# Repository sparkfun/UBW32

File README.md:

USB 32-Bit Whacker-PIC32MX795 Development Board
================================================

[
*USB 32-Bit Whacker (DEV-09713)*](https://www.sparkfun.com/products/9713)

This breadboard friendly development board enables you to get the PIC32 up and running quickly. 
Power can be provided over USB, there are 3 push buttons (including 2 user-defined buttons),
and 5 indicator LEDs. The board comes pre-loaded with a USB bootloader and special UBW firmware that accepts
simple serial commands to control the various I/O functions. 

Repository Contents
-------------------
* **/Hardware** - All Eagle design files (.brd, .sch, .STL)

License Information
-------------------
Distributed as-is; no warranty is given.

This product is a collaboration with Brian Schmalz.

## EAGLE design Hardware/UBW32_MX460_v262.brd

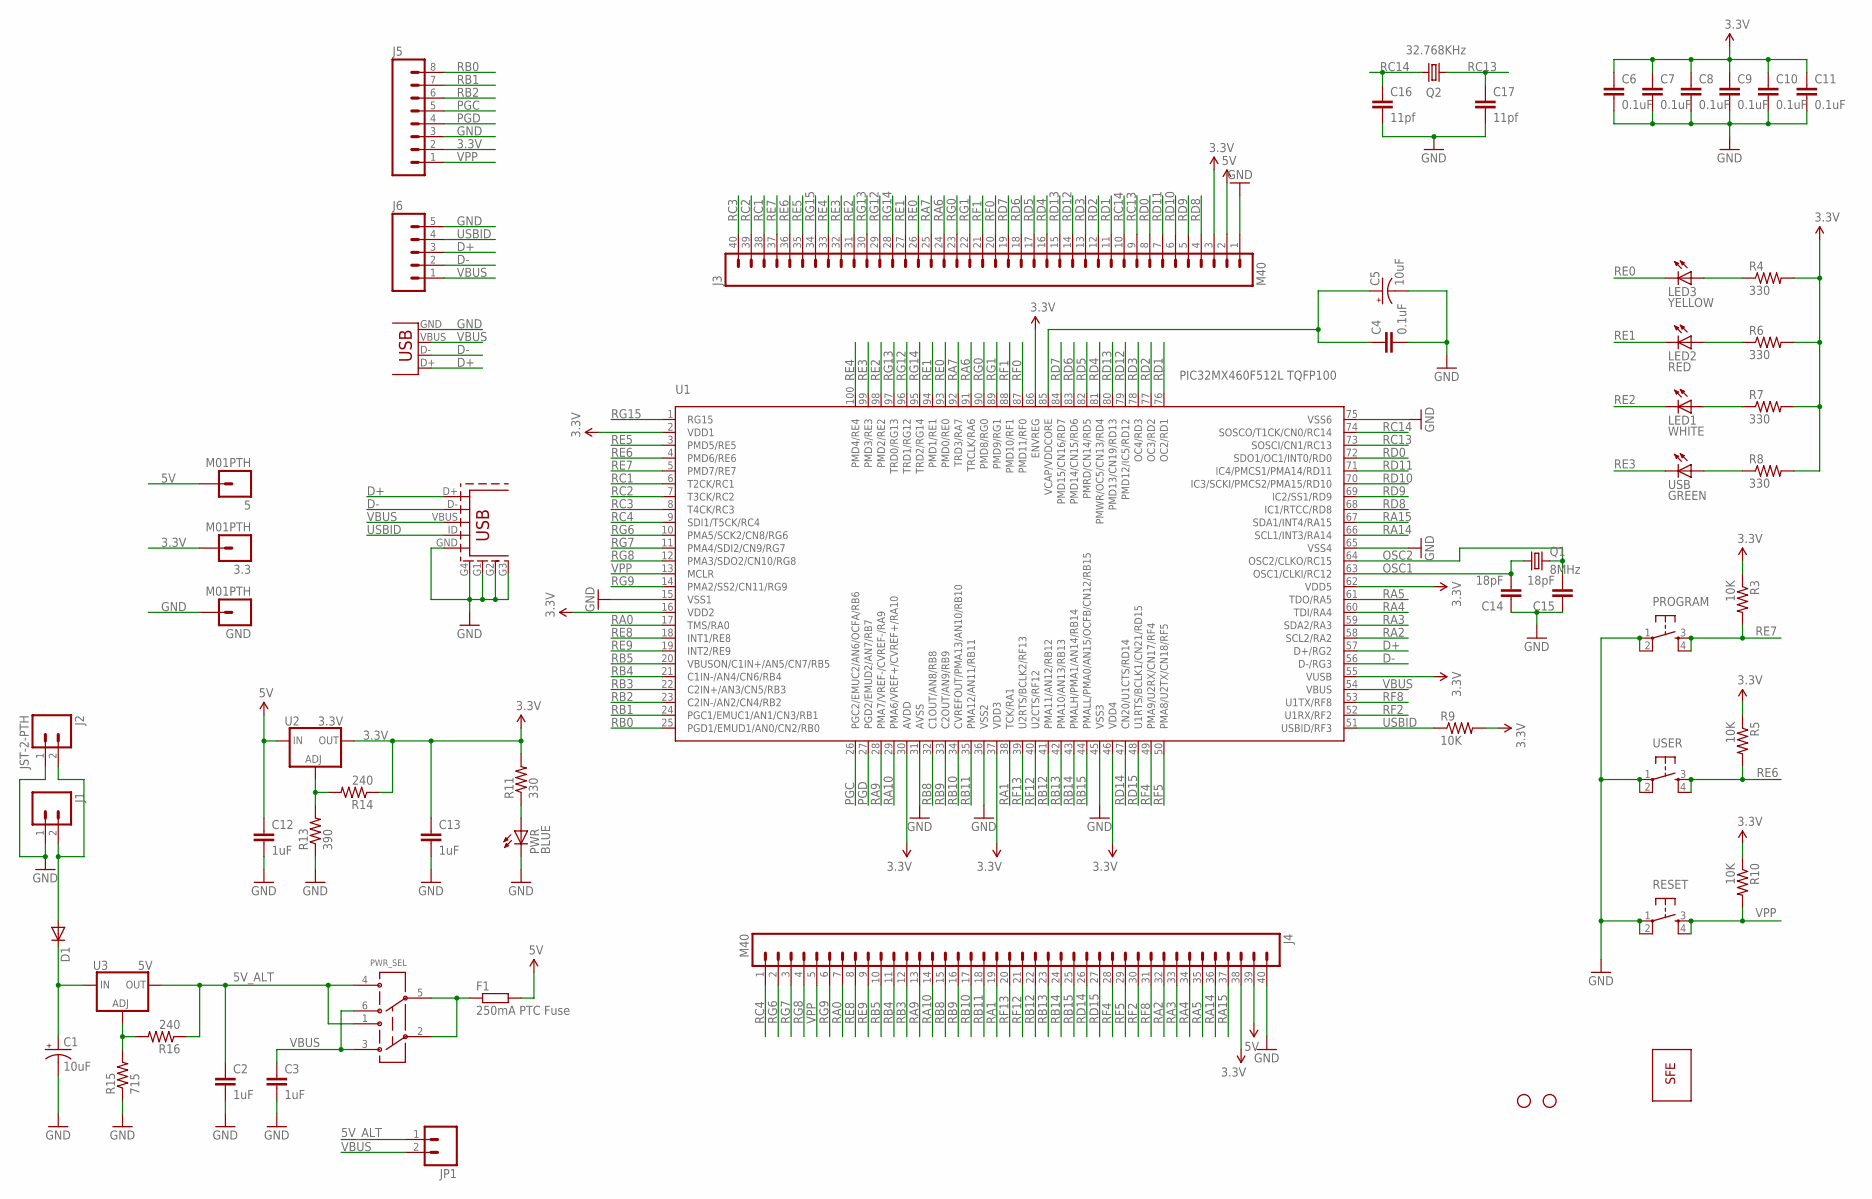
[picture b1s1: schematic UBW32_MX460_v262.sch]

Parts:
3.3, 5: M01PTH; 1X01
C1, C5: 10uF; EIA3528
C2, C3: 1uF; 0402-CAP
C4, C6, C7, C8, C9, C11: 0.1uF; 0402-CAP
C10: 0.1uF; C0402
C12, C13: 1uF; C0402
C14, C15: 18pF; 0402-CAP
C16, C17: 11pf; 0402-CAP
D1: DIODESMA; SMA-DIODE
F1: 250mA PTC Fuse; R1206
GND: M01PTH; 1X01
J1: M02PTH; 1X02
J2: JST-2-PTH; S2B-PH
J3, J4: M40; 1X40
J5: M08; 1X08
J6: M05PTH; 1X05
J7: USB-A-S
J8: USB-MINIB
JP1: M02PTH; 1X02
LED1: WHITE; LED-0603
LED2: RED; LED-0603
LED3: YELLOW; LED-0603
PROGRAM: TAC_SWITCHSND; TACTILE_SWITCH_SMD
PWR: BLUE; LED-0603
PWR_SEL: AYZ0202
Q1: 8MHz; CRYSTAL-SMD-5X3
Q2: 32.768KHz; CRYSTAL-32KHZ-SMD
R3, R5, R9, R10: 10K; 0402-RES
R4, R6, R7, R8, R11: 330; 0402-RES
R13: 390; 0402-RES
R14, R16: 240; 0402-RES
R15: 715; 0402-RES
RESET: TAC_SWITCHSND; TACTILE_SWITCH_SMD
U1: PIC32MX460F512L TQFP100; TQFP100
U2: 3.3V; SOT223
U3: 5V; SOT223
U$4: LOGO-SFENEW; SFE-NEW-WEBLOGO
U$6, U$7: STAND-OFF
USB: GREEN; LED-0603
USER: TAC_SWITCHSND; TACTILE_SWITCH_SMD

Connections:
3.3V: 3.3.1, C6.1, C7.1, C8.1, C9.1, C10.1, C11.1, C13.1, J3.3, J4.38, J5.2, R3.1, R4.2, R5.1, R6.2, R7.2, R8.2, R9.2, R10.1, R11.2, R14.1, U1.2 (VDD1), U1.16 (VDD2), U1.30 (AVDD), U1.37 (VDD3), U1.46 (VDD4), U1.55 (VUSB), U1.62 (VDD5), U1.86 (ENVREG), U2.2 (OUT)
5V: 5.1, C12.1, F1.2, J3.2, J4.39, U2.3 (IN)
5V_ALT: C2.1, JP1.1, PWR_SEL.1 (3), PWR_SEL.4 (6), R16.1, U3.2 (OUT)
D+: J6.3, J7.D+, J8.D+, U1.57 (D+/RG2)
D-: J6.2, J7.D-, J8.D-, U1.56 (D-/RG3)
GND: C1.C (-), C2.2, C3.2, C4.2, C5.C (-), C6.2, C7.2, C8.2, C9.2, C10.2, C11.2, C12.2, C13.2, C14.1, C15.1, C16.2, C17.2, GND.1, J1.1, J2.1, J3.1, J4.40, J5.3, J6.5, J7.GND, J8.G1, J8.G2, J8.G3, J8.G4 (SHIELD), J8.GND, PROGRAM.1, PROGRAM.2, PWR.C, R13.1, R15.1, RESET.1, RESET.2, U1.15 (VSS1), U1.31 (AVSS), U1.36 (VSS2), U1.45 (VSS3), U1.65 (VSS4), U1.75 (VSS6), USER.1, USER.2
unnamed: D1.A, J1.2, J2.2
unnamed: F1.1, PWR_SEL.2, PWR_SEL.5
unnamed: R13.2, R14.2, U2.1 (ADJ)
unnamed: R15.2, R16.2, U3.1 (ADJ)
unnamed: PWR.A, R11.1
unnamed: R8.1, USB.A
unnamed: LED1.A, R7.1
unnamed: LED2.A, R6.1
unnamed: LED3.A, R4.1
unnamed: C4.1, C5.A (+), U1.85 (VCAP/VDDCORE)
OSC1: C14.2, Q1.1, U1.63 (OSC1/CLKI/RC12)
OSC2: C15.2, Q1.3 (2), U1.64 (OSC2/CLKO/RC15)
PGC: J5.5, U1.26 (PGC2/EMUC2/AN6/OCFA/RB6)
PGD: J5.4, U1.27 (PGD2/EMUD2/AN7/RB7)
RA0: J4.7, U1.17 (TMS/RA0)
RA1: J4.19, U1.38 (TCK/RA1)
RA2: J4.32, U1.58 (SCL2/RA2)
RA3: J4.33, U1.59 (SDA2/RA3)
RA4: J4.34, U1.60 (TDI/RA4)
RA5: J4.35, U1.61 (TDO/RA5)
RA6: J3.24, U1.91 (TRCLK/RA6)
RA7: J3.25, U1.92 (TRD3/RA7)
RA9: J4.13, U1.28 (PMA7/VREF-/CVREF-/RA9)
RA10: J4.14, U1.29 (PMA6/VREF+/CVREF+/RA10)
RA14: J4.36, U1.66 (SCL1/INT3/RA14)
RA15: J4.37, U1.67 (SDA1/INT4/RA15)
RB0: J5.8, U1.25 (PGD1/EMUD1/AN0/CN2/RB0)
RB1: J5.7, U1.24 (PGC1/EMUC1/AN1/CN3/RB1)
RB2: J5.6, U1.23 (C2IN-/AN2/CN4/RB2)
RB3: J4.12, U1.22 (C2IN+/AN3/CN5/RB3)
RB4: J4.11, U1.21 (C1IN-/AN4/CN6/RB4)
RB5: J4.10, U1.20 (VBUSON/C1IN+/AN5/CN7/RB5)
RB8: J4.15, U1.32 (C1OUT/AN8/RB8)
RB9: J4.16, U1.33 (C2OUT/AN9/RB9)
RB10: J4.17, U1.34 (CVREFOUT/PMA13/AN10/RB10)
RB11: J4.18, U1.35 (PMA12/AN11/RB11)
RB12: J4.22, U1.41 (PMA11/AN12/RB12)
RB13: J4.23, U1.42 (PMA10/AN13/RB13)
RB14: J4.24, U1.43 (PMALH/PMA1/AN14/RB14)
RB15: J4.25, U1.44 (PMALL/PMA0/AN15/OCFB/CN12/RB15)
RC1: J3.38, U1.6 (T2CK/RC1)
RC2: J3.39, U1.7 (T3CK/RC2)
RC3: J3.40, U1.8 (T4CK/RC3)
RC4: J4.1, U1.9 (SDI1/T5CK/RC4)
RC13: C17.1, J3.9, Q2.X1 (1), U1.73 (SOSCI/CN1/RC13)
RC14: C16.1, J3.10, Q2.X2 (2), U1.74 (SOSCO/T1CK/CN0/RC14)
RD0: J3.8, U1.72 (SDO1/OC1/INT0/RD0)
RD1: J3.11, U1.76 (OC2/RD1)
RD2: J3.12, U1.77 (OC3/RD2)
RD3: J3.13, U1.78 (OC4/RD3)
RD4: J3.16, U1.81 (PMWR/OC5/CN13/RD4)
RD5: J3.17, U1.82 (PMRD/CN14/RD5)
RD6: J3.18, U1.83 (PMD14/CN15/RD6)
RD7: J3.19, U1.84 (PMD15/CN16/RD7)
RD8: J3.4, U1.68 (IC1/RTCC/RD8)
RD9: J3.5, U1.69 (IC2/SS1/RD9)
RD10: J3.6, U1.70 (IC3/SCKI/PMCS2/PMA15/RD10)
RD11: J3.7, U1.71 (IC4/PMCS1/PMA14/RD11)
RD12: J3.14, U1.79 (PMD12/IC5/RD12)
RD13: J3.15, U1.80 (PMD13/CN19/RD13)
RD14: J4.26, U1.47 (CN20/U1CTS/RD14)
RD15: J4.27, U1.48 (U1RTS/BCLK1/CN21/RD15)
RE0: J3.26, LED3.C, U1.93 (PMD0/RE0)
RE1: J3.27, LED2.C, U1.94 (PMD1/RE1)
RE2: J3.31, LED1.C, U1.98 (PMD2/RE2)
RE3: J3.32, U1.99 (PMD3/RE3), USB.C
RE4: J3.33, U1.100 (PMD4/RE4)
RE5: J3.35, U1.3 (PMD5/RE5)
RE6: J3.36, R5.2, U1.4 (PMD6/RE6), USER.3, USER.4
RE7: J3.37, PROGRAM.3, PROGRAM.4, R3.2, U1.5 (PMD7/RE7)
RE8: J4.8, U1.18 (INT1/RE8)
RE9: J4.9, U1.19 (INT2/RE9)
RF0: J3.20, U1.87 (PMD11/RF0)
RF1: J3.21, U1.88 (PMD10/RF1)
RF2: J4.30, U1.52 (U1RX/RF2)
RF4: J4.28, U1.49 (PMA9/U2RX/CN17/RF4)
RF5: J4.29, U1.50 (PMA8/U2TX/CN18/RF5)
RF8: J4.31, U1.53 (U1TX/RF8)
RF12: J4.21, U1.40 (U2CTS/RF12)
RF13: J4.20, U1.39 (U2RTS/BCLK2/RF13)
RG0: J3.23, U1.90 (PMD8/RG0)
RG1: J3.22, U1.89 (PMD9/RG1)
RG6: J4.2, U1.10 (PMA5/SCK2/CN8/RG6)
RG7: J4.3, U1.11 (PMA4/SDI2/CN9/RG7)
RG8: J4.4, U1.12 (PMA3/SDO2/CN10/RG8)
RG9: J4.6, U1.14 (PMA2/SS2/CN11/RG9)
RG12: J3.29, U1.96 (TRD1/RG12)
RG13: J3.30, U1.97 (TRD0/RG13)
RG14: J3.28, U1.95 (TRD2/RG14)
RG15: J3.34, U1.1 (RG15)
USBID: J6.4, J8.ID (USB_ID), R9.1, U1.51 (USBID/RF3)
VBUS: C3.1, J6.1, J7.VBUS, J8.VBUS, JP1.2, PWR_SEL.3 (1), PWR_SEL.6 (4), U1.54 (VBUS)
VIN_RAW: C1.A (+), D1.C, U3.3 (IN)
VPP: J4.5, J5.1, R10.2, RESET.3, RESET.4, U1.13 (MCLR)

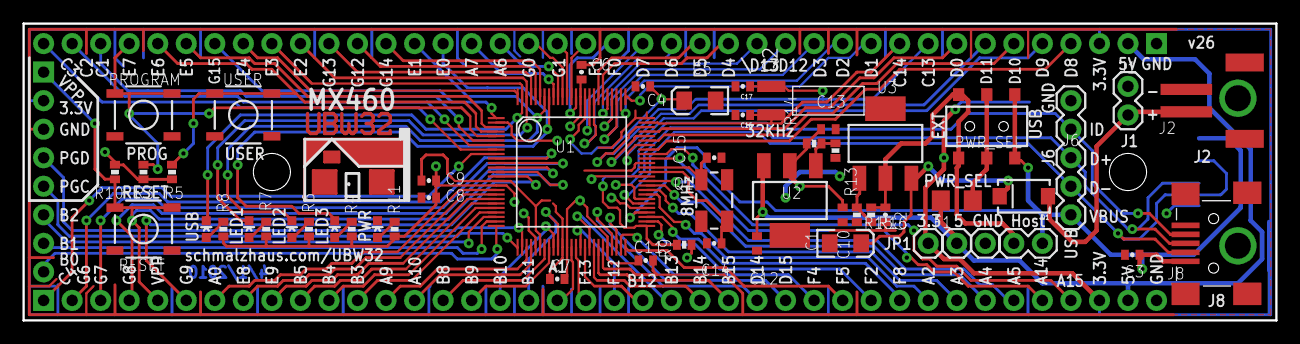
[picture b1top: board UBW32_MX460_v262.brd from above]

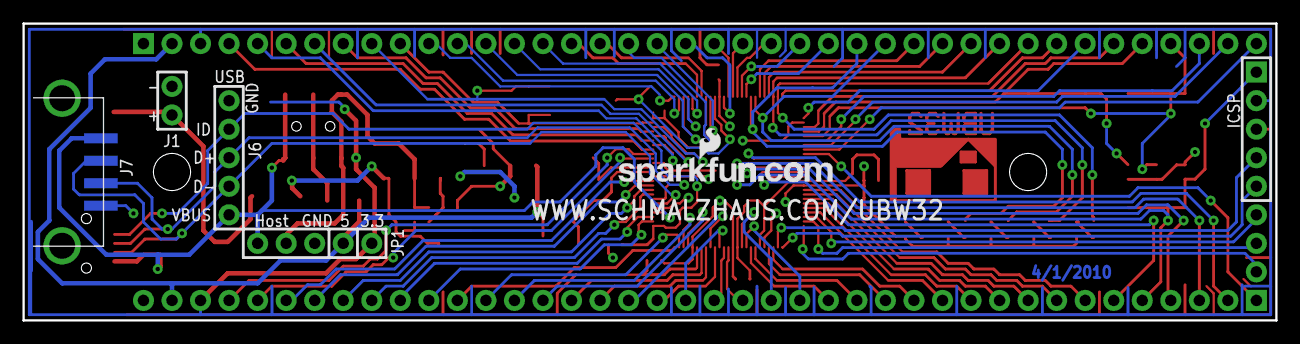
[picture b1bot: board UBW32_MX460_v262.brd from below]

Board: 2 copper layers, 111.5 x 26.4 mm, 63 parts (2 on the bottom side), 100 nets.

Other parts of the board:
U$3: UBW32
U$5: SCHMALZHAUS

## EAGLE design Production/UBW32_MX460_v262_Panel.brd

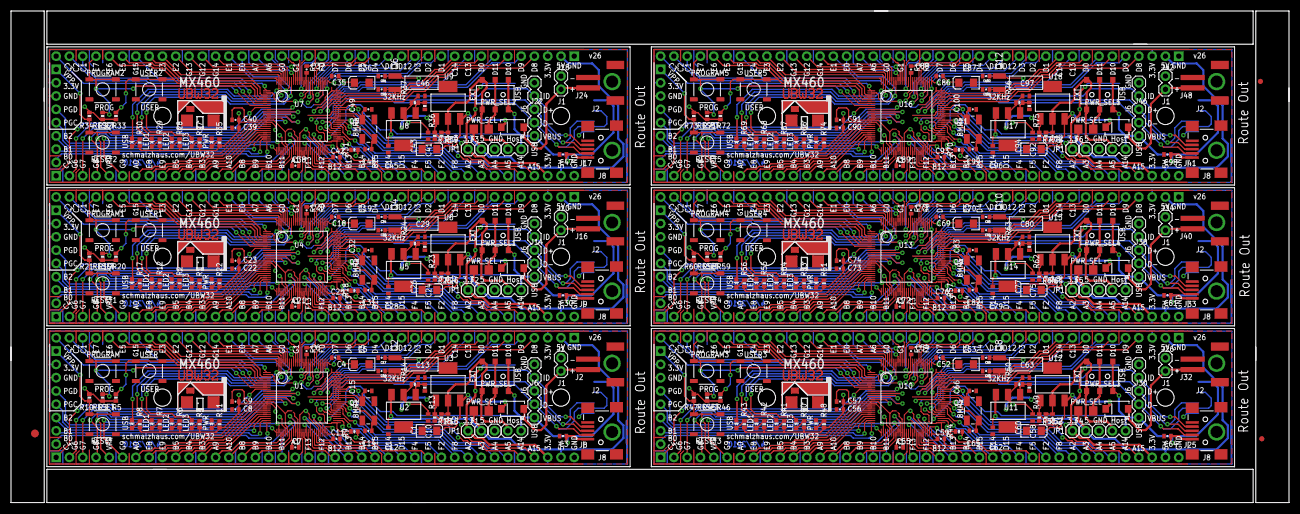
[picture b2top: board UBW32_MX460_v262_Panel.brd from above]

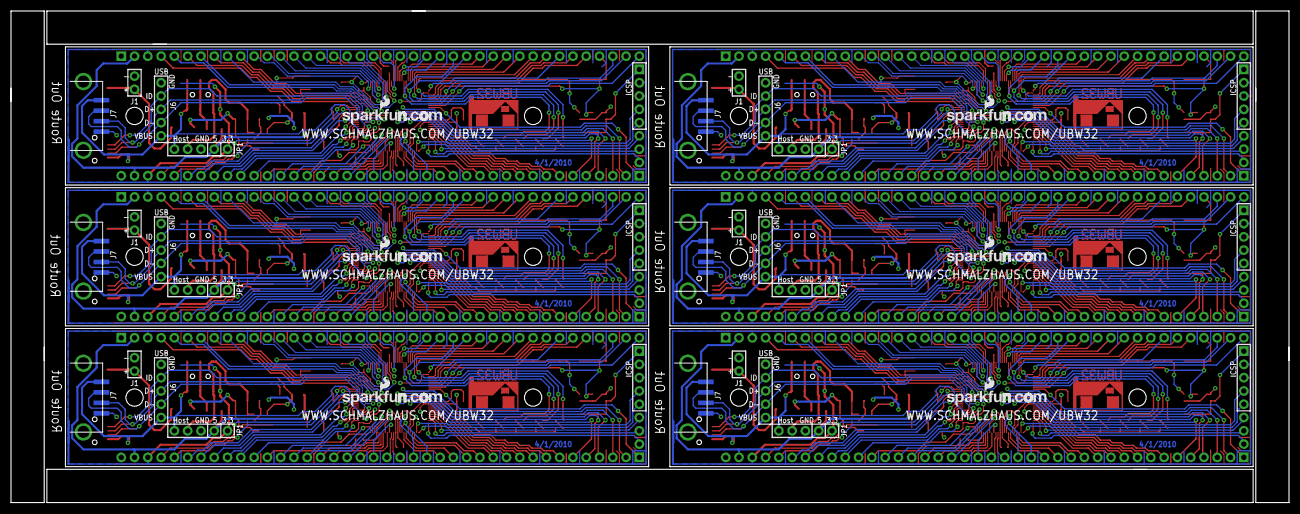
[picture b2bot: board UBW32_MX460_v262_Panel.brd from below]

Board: 2 copper layers, 244.3 x 94.0 mm, 381 parts (12 on the bottom side), 600 nets.

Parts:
1, 2, 3, 3.1, 3.2, 3.3, 3.4, 3.5, 3.6, 4, 5, 6: M01PTH; 1X01
C1, C5, C19, C26, C36, C43, C53, C60, C70, C77, C87, C94: 10uF; EIA3216
C2, C3, C27, C30, C44, C47, C61, C64, C78, C81, C95, C98: 1uF; 0402-CAP
C4, C6, C7, C8, C9, C11, C18, C20, C21, C22, C23, C25, C35, C37, C38, C39, C40, C42, C52, C54, C55, C56, C57, C59, C69, C71, C72, C73, C74, C76, C86, C88, C89, C90, C91, C93: 0.1uF; 0402-CAP
C10, C24, C41, C58, C75, C92: 0.1uF; C0402
C12, C13, C28, C29, C45, C46, C62, C63, C79, C80, C96, C97: 1uF; C0402
C14, C15, C31, C32, C48, C49, C65, C66, C82, C83, C99, C100: 18pF; 0402-CAP
C16, C17, C33, C34, C50, C51, C67, C68, C84, C85, C101, C102: 11pf; 0402-CAP
D1, D2, D3, D4, D5, D6: SMA-DIODE
E$1: FIDUCIAL-1.5X3
E$5, E$6: FIDUCIAL-1X2
F1, F2, F3, F4, F5, F6: 250mA PTC Fuse; R1206
GND, GND1, GND2, GND3, GND4, GND5: M01PTH; 1X01
J1, J10, J18, J26, J34, J42: 1X02
J2, J16, J24, J32, J40, J48: S2B-PH
J3, J4, J11, J12, J19, J20, J27, J28, J35, J36, J43, J44: M40; 1X40
J5, J13, J21, J29, J37, J45: 1X08
J6, J14, J22, J30, J38, J46: 1X05
J7, J15, J23, J31, J39, J47: USB-A-S
J8, J9, J17, J25, J33, J41: USB-MINIB
JP1, JP2, JP3, JP4, JP5, JP6: 1X02
LED1, LED6, LED9, LED12, LED15, LED18: WHITE; LED-0603
LED2, LED5, LED8, LED11, LED14, LED17: RED; LED-0603
LED3, LED4, LED7, LED10, LED13, LED16: YELLOW; LED-0603
PROGRAM, PROGRAM1, PROGRAM2, PROGRAM3, PROGRAM4, PROGRAM5: TACTILE_SWITCH_SMD
PWR, PWR1, PWR2, PWR3, PWR4, PWR5: BLUE; LED-0603
PWR_SEL, PWR_SEL1, PWR_SEL2, PWR_SEL3, PWR_SEL4, PWR_SEL5: AYZ0202
Q1, Q3, Q5, Q7, Q9, Q11: 8MHz; CRYSTAL-SMD-5X3
Q2, Q4, Q6, Q8, Q10, Q12: 32.768KHz; CRYSTAL-32KHZ-SMD
R1, R2, R4, R6, R7, R8, R11, R12, R17, R22, R27, R28, R29, R30, R35, R40, R41, R42, R43, R48, R53, R54, R55, R56, R61, R66, R67, R68, R69, R74: 330; 0402-RES
R3, R5, R9, R10, R18, R19, R20, R21, R31, R32, R33, R34, R44, R45, R46, R47, R57, R58, R59, R60, R70, R71, R72, R73: 10K; 0402-RES
R13, R23, R36, R49, R62, R75: 390; 0402-RES
R14, R16, R24, R26, R37, R39, R50, R52, R63, R65, R76, R78: 240; 0402-RES
R15, R25, R38, R51, R64, R77: 715; 0402-RES
RESET, RESET1, RESET2, RESET3, RESET4, RESET5: TACTILE_SWITCH_SMD
U1, U4, U7, U10, U13, U16: PIC32MX460F512L TQFP100; TQFP100
U2, U5, U8, U11, U14, U17: 3.3V; SOT223
U3, U6, U9, U12, U15, U18: 5V; SOT223
U$1, U$2, U$6, U$7, U$11, U$12, U$16, U$17, U$21, U$22, U$26, U$27: STAND-OFF
U$3, U$9, U$14, U$19, U$24, U$29: UBW32
U$4, U$8, U$13, U$18, U$23, U$28: LOGO-SFENEW; SFE-NEW-WEBLOGO
U$5, U$10, U$15, U$20, U$25, U$30: SCHMALZHAUS
USB, USB1, USB2, USB3, USB4, USB5: GREEN; LED-0603
USER, USER1, USER2, USER3, USER4, USER5: TACTILE_SWITCH_SMD

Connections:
3.3V: 3.3.1, C6.1, C7.1, C8.1, C9.1, C10.1, C11.1, C13.1, J3.3, J4.38, J5.2, R3.1, R4.2, R5.1, R6.2, R7.2, R8.2, R9.2, R10.1, R11.2, R14.1, U1.2, U1.16, U1.30, U1.37, U1.46, U1.55, U1.62, U1.86, U2.2
3.3V1: 3.1.1, C20.1, C21.1, C22.1, C23.1, C24.1, C25.1, C29.1, J11.3, J12.38, J13.2, R1.2, R2.2, R12.2, R17.2, R18.2, R19.1, R20.1, R21.1, R22.2, R24.1, U4.2, U4.16, U4.30, U4.37, U4.46, U4.55, U4.62, U4.86, U5.2
3.3V2: 3.2.1, C37.1, C38.1, C39.1, C40.1, C41.1, C42.1, C46.1, J19.3, J20.38, J21.2, R27.2, R28.2, R29.2, R30.2, R31.2, R32.1, R33.1, R34.1, R35.2, R37.1, U7.2, U7.16, U7.30, U7.37, U7.46, U7.55, U7.62, U7.86, U8.2
3.3V3: 3.4.1, C54.1, C55.1, C56.1, C57.1, C58.1, C59.1, C63.1, J27.3, J28.38, J29.2, R40.2, R41.2, R42.2, R43.2, R44.2, R45.1, R46.1, R47.1, R48.2, R50.1, U10.2, U10.16, U10.30, U10.37, U10.46, U10.55, U10.62, U10.86, U11.2
3.3V4: 3.5.1, C71.1, C72.1, C73.1, C74.1, C75.1, C76.1, C80.1, J35.3, J36.38, J37.2, R53.2, R54.2, R55.2, R56.2, R57.2, R58.1, R59.1, R60.1, R61.2, R63.1, U13.2, U13.16, U13.30, U13.37, U13.46, U13.55, U13.62, U13.86, U14.2
3.3V5: 3.6.1, C88.1, C89.1, C90.1, C91.1, C92.1, C93.1, C97.1, J43.3, J44.38, J45.2, R66.2, R67.2, R68.2, R69.2, R70.2, R71.1, R72.1, R73.1, R74.2, R76.1, U16.2, U16.16, U16.30, U16.37, U16.46, U16.55, U16.62, U16.86, U17.2
5V: 5.1, C12.1, F1.2, J3.2, J4.39, U2.3
5V1: 1.1, C28.1, F2.2, J11.2, J12.39, U5.3
5V2: 2.1, C45.1, F3.2, J19.2, J20.39, U8.3
5V3: 3.1, C62.1, F4.2, J27.2, J28.39, U11.3
5V4: 4.1, C79.1, F5.2, J35.2, J36.39, U14.3
5V5: 6.1, C96.1, F6.2, J43.2, J44.39, U17.3
5V_ALT: C2.1, JP1.1, PWR_SEL.1, PWR_SEL.4, R16.1, U3.2
5V_ALT1: C27.1, JP2.1, PWR_SEL1.1, PWR_SEL1.4, R26.1, U6.2
5V_ALT2: C44.1, JP3.1, PWR_SEL2.1, PWR_SEL2.4, R39.1, U9.2
5V_ALT3: C61.1, JP4.1, PWR_SEL3.1, PWR_SEL3.4, R52.1, U12.2
5V_ALT4: C78.1, JP5.1, PWR_SEL4.1, PWR_SEL4.4, R65.1, U15.2
5V_ALT5: C95.1, JP6.1, PWR_SEL5.1, PWR_SEL5.4, R78.1, U18.2
D+: J6.3, J7.D+, J8.D+, U1.57
D+1: J9.D+, J14.3, J15.D+, U4.57
D+2: J17.D+, J22.3, J23.D+, U7.57
D+3: J25.D+, J30.3, J31.D+, U10.57
D+4: J33.D+, J38.3, J39.D+, U13.57
D+5: J41.D+, J46.3, J47.D+, U16.57
D-: J6.2, J7.D-, J8.D-, U1.56
D-1: J9.D-, J14.2, J15.D-, U4.56
D-2: J17.D-, J22.2, J23.D-, U7.56
D-3: J25.D-, J30.2, J31.D-, U10.56
D-4: J33.D-, J38.2, J39.D-, U13.56
D-5: J41.D-, J46.2, J47.D-, U16.56
GND: C1.C, C2.2, C3.2, C4.2, C5.C, C6.2, C7.2, C8.2, C9.2, C10.2, C11.2, C12.2, C13.2, C14.1, C15.1, C16.2, C17.2, GND.1, J1.1, J2.1, J3.1, J4.40, J5.3, J6.5, J7.GND, J8.G1, J8.G2, J8.G3, J8.G4, J8.GND, PROGRAM.1, PROGRAM.2, PWR.C, R13.1, R15.1, RESET.1, RESET.2, U1.15, U1.31, U1.36, U1.45, U1.65, U1.75, USER.1, USER.2
GND1: C18.2, C19.C, C20.2, C21.2, C22.2, C23.2, C24.2, C25.2, C26.C, C27.2, C28.2, C29.2, C30.2, C31.1, C32.1, C33.2, C34.2, GND1.1, J9.G1, J9.G2, J9.G3, J9.G4, J9.GND, J10.1, J11.1, J12.40, J13.3, J14.5, J15.GND, J16.1, PROGRAM1.1, PROGRAM1.2, PWR1.C, R23.1, R25.1, RESET1.1, RESET1.2, U4.15, U4.31, U4.36, U4.45, U4.65, U4.75, USER1.1, USER1.2
GND2: C35.2, C36.C, C37.2, C38.2, C39.2, C40.2, C41.2, C42.2, C43.C, C44.2, C45.2, C46.2, C47.2, C48.1, C49.1, C50.2, C51.2, GND2.1, J17.G1, J17.G2, J17.G3, J17.G4, J17.GND, J18.1, J19.1, J20.40, J21.3, J22.5, J23.GND, J24.1, PROGRAM2.1, PROGRAM2.2, PWR2.C, R36.1, R38.1, RESET2.1, RESET2.2, U7.15, U7.31, U7.36, U7.45, U7.65, U7.75, USER2.1, USER2.2
GND3: C52.2, C53.C, C54.2, C55.2, C56.2, C57.2, C58.2, C59.2, C60.C, C61.2, C62.2, C63.2, C64.2, C65.1, C66.1, C67.2, C68.2, GND3.1, J25.G1, J25.G2, J25.G3, J25.G4, J25.GND, J26.1, J27.1, J28.40, J29.3, J30.5, J31.GND, J32.1, PROGRAM3.1, PROGRAM3.2, PWR3.C, R49.1, R51.1, RESET3.1, RESET3.2, U10.15, U10.31, U10.36, U10.45, U10.65, U10.75, USER3.1, USER3.2
GND4: C69.2, C70.C, C71.2, C72.2, C73.2, C74.2, C75.2, C76.2, C77.C, C78.2, C79.2, C80.2, C81.2, C82.1, C83.1, C84.2, C85.2, GND4.1, J33.G1, J33.G2, J33.G3, J33.G4, J33.GND, J34.1, J35.1, J36.40, J37.3, J38.5, J39.GND, J40.1, PROGRAM4.1, PROGRAM4.2, PWR4.C, R62.1, R64.1, RESET4.1, RESET4.2, U13.15, U13.31, U13.36, U13.45, U13.65, U13.75, USER4.1, USER4.2
GND5: C86.2, C87.C, C88.2, C89.2, C90.2, C91.2, C92.2, C93.2, C94.C, C95.2, C96.2, C97.2, C98.2, C99.1, C100.1, C101.2, C102.2, GND5.1, J41.G1, J41.G2, J41.G3, J41.G4, J41.GND, J42.1, J43.1, J44.40, J45.3, J46.5, J47.GND, J48.1, PROGRAM5.1, PROGRAM5.2, PWR5.C, R75.1, R77.1, RESET5.1, RESET5.2, U16.15, U16.31, U16.36, U16.45, U16.65, U16.75, USER5.1, USER5.2
unnamed: D1.A, J1.2, J2.2
unnamed: F1.1, PWR_SEL.2, PWR_SEL.5
unnamed: R13.2, R14.2, U2.1
unnamed: R15.2, R16.2, U3.1
unnamed: C18.1, C19.A, U4.85
unnamed: PWR.A, R11.1
unnamed: R17.1, USB1.A
unnamed: LED6.A, R12.1
unnamed: LED5.A, R2.1
unnamed: LED4.A, R1.1
unnamed: PWR1.A, R22.1
unnamed: D2.A, J10.2, J16.2
unnamed: F2.1, PWR_SEL1.2, PWR_SEL1.5
unnamed: R23.2, R24.2, U5.1
unnamed: R25.2, R26.2, U6.1
unnamed: C35.1, C36.A, U7.85
unnamed: R30.1, USB2.A
unnamed: LED9.A, R29.1
unnamed: LED8.A, R28.1
unnamed: R8.1, USB.A
unnamed: LED7.A, R27.1
unnamed: LED1.A, R7.1
unnamed: LED2.A, R6.1
unnamed: PWR2.A, R35.1
unnamed: D3.A, J18.2, J24.2
unnamed: F3.1, PWR_SEL2.2, PWR_SEL2.5
unnamed: R36.2, R37.2, U8.1
unnamed: R38.2, R39.2, U9.1
unnamed: C52.1, C53.A, U10.85
unnamed: R43.1, USB3.A
unnamed: LED12.A, R42.1
unnamed: LED11.A, R41.1
unnamed: LED10.A, R40.1
unnamed: PWR3.A, R48.1
unnamed: LED3.A, R4.1
unnamed: D4.A, J26.2, J32.2
unnamed: F4.1, PWR_SEL3.2, PWR_SEL3.5
unnamed: R49.2, R50.2, U11.1
unnamed: R51.2, R52.2, U12.1
unnamed: C69.1, C70.A, U13.85
unnamed: R56.1, USB4.A
unnamed: LED15.A, R55.1
unnamed: LED14.A, R54.1
unnamed: LED13.A, R53.1
unnamed: PWR4.A, R61.1
unnamed: D5.A, J34.2, J40.2
unnamed: F5.1, PWR_SEL4.2, PWR_SEL4.5
unnamed: R62.2, R63.2, U14.1
unnamed: R64.2, R65.2, U15.1
unnamed: C86.1, C87.A, U16.85
unnamed: R69.1, USB5.A
unnamed: LED18.A, R68.1
unnamed: LED17.A, R67.1
unnamed: LED16.A, R66.1
unnamed: PWR5.A, R74.1
unnamed: D6.A, J42.2, J48.2
unnamed: F6.1, PWR_SEL5.2, PWR_SEL5.5
unnamed: R75.2, R76.2, U17.1
unnamed: R77.2, R78.2, U18.1
unnamed: C4.1, C5.A, U1.85
OSC1: C14.2, Q1.1, U1.63
OSC2: C15.2, Q1.3, U1.64
OSC3: C32.2, Q3.3, U4.64
OSC4: C31.2, Q3.1, U4.63
OSC5: C49.2, Q5.3, U7.64
OSC6: C48.2, Q5.1, U7.63
OSC7: C66.2, Q7.3, U10.64
OSC8: C65.2, Q7.1, U10.63
OSC9: C83.2, Q9.3, U13.64
OSC10: C82.2, Q9.1, U13.63
OSC11: C100.2, Q11.3, U16.64
OSC12: C99.2, Q11.1, U16.63
PGC: J5.5, U1.26
PGC1: J13.5, U4.26
PGC2: J21.5, U7.26
PGC3: J29.5, U10.26
PGC4: J37.5, U13.26
PGC5: J45.5, U16.26
PGD: J5.4, U1.27
PGD1: J13.4, U4.27
PGD2: J21.4, U7.27
PGD3: J29.4, U10.27
PGD4: J37.4, U13.27
PGD5: J45.4, U16.27
RA0: J4.7, U1.17
RA1: J4.19, U1.38
RA2: J4.32, U1.58
RA3: J4.33, U1.59
RA4: J4.34, U1.60
RA5: J4.35, U1.61
RA6: J3.24, U1.91
RA7: J3.25, U1.92
RA8: J12.32, U4.58
RA9: J4.13, U1.28
RA10: J4.14, U1.29
RA11: J12.33, U4.59
RA12: J11.24, U4.91
RA13: J11.25, U4.92
RA14: J4.36, U1.66
RA15: J4.37, U1.67
RA16: J12.34, U4.60
RA17: J12.35, U4.61
RA18: J12.7, U4.17
RA19: J12.13, U4.28
RA20: J12.14, U4.29
RA21: J12.19, U4.38
RA22: J12.36, U4.66
RA23: J12.37, U4.67
RA24: J20.32, U7.58
RA25: J20.33, U7.59
RA26: J19.24, U7.91
RA27: J19.25, U7.92
RA28: J20.34, U7.60
RA29: J20.35, U7.61
RA30: J20.7, U7.17
RA31: J20.13, U7.28
RA32: J20.14, U7.29
RA33: J20.19, U7.38
RA34: J20.36, U7.66
RA35: J20.37, U7.67
RA36: J28.32, U10.58
RA37: J28.33, U10.59
RA38: J27.24, U10.91
RA39: J27.25, U10.92
RA40: J28.34, U10.60
RA41: J28.35, U10.61
RA42: J28.7, U10.17
RA43: J28.13, U10.28
RA44: J28.14, U10.29
RA45: J28.19, U10.38
RA46: J28.36, U10.66
RA47: J28.37, U10.67
RA48: J36.32, U13.58
RA49: J36.33, U13.59
RA50: J35.24, U13.91
RA51: J35.25, U13.92
RA52: J36.34, U13.60
RA53: J36.35, U13.61
RA54: J36.7, U13.17
RA55: J36.13, U13.28
RA56: J36.14, U13.29
RA57: J36.19, U13.38
RA58: J36.36, U13.66
RA59: J36.37, U13.67
RA60: J44.32, U16.58
RA61: J44.33, U16.59
RA62: J43.24, U16.91
RA63: J43.25, U16.92
RA64: J44.34, U16.60
RA65: J44.35, U16.61
RA66: J44.7, U16.17
RA67: J44.13, U16.28
RA68: J44.14, U16.29
RA69: J44.19, U16.38
RA70: J44.36, U16.66
RA71: J44.37, U16.67
RB0: J5.8, U1.25
RB1: J5.7, U1.24
RB2: J5.6, U1.23
RB3: J4.12, U1.22
RB4: J4.11, U1.21
RB5: J4.10, U1.20
RB6: J13.8, U4.25
RB7: J13.7, U4.24
RB8: J4.15, U1.32
RB9: J4.16, U1.33
RB10: J4.17, U1.34
RB11: J4.18, U1.35
RB12: J4.22, U1.41
RB13: J4.23, U1.42
RB14: J4.24, U1.43
RB15: J4.25, U1.44
RB16: J12.10, U4.20
RB17: J12.11, U4.21
RB18: J12.12, U4.22
RB19: J13.6, U4.23
RB20: J12.15, U4.32
RB21: J12.16, U4.33
RB22: J12.17, U4.34
RB23: J12.18, U4.35
RB24: J12.22, U4.41
RB25: J12.23, U4.42
RB26: J12.24, U4.43
RB27: J12.25, U4.44
RB28: J21.8, U7.25
RB29: J21.7, U7.24
RB30: J20.10, U7.20
RB31: J20.11, U7.21
RB32: J20.12, U7.22
RB33: J21.6, U7.23
RB34: J20.15, U7.32
RB35: J20.16, U7.33
RB36: J20.17, U7.34
RB37: J20.18, U7.35
RB38: J20.22, U7.41
RB39: J20.23, U7.42
RB40: J20.24, U7.43
RB41: J20.25, U7.44
RB42: J29.8, U10.25
RB43: J29.7, U10.24
RB44: J28.10, U10.20
RB45: J28.11, U10.21
RB46: J28.12, U10.22
RB47: J29.6, U10.23
RB48: J28.15, U10.32
RB49: J28.16, U10.33
RB50: J28.17, U10.34
RB51: J28.18, U10.35
RB52: J28.22, U10.41
RB53: J28.23, U10.42
RB54: J28.24, U10.43
RB55: J28.25, U10.44
RB56: J37.8, U13.25
RB57: J37.7, U13.24
RB58: J36.10, U13.20
RB59: J36.11, U13.21
RB60: J36.12, U13.22
RB61: J37.6, U13.23
RB62: J36.15, U13.32
RB63: J36.16, U13.33
RB64: J36.17, U13.34
RB65: J36.18, U13.35
RB66: J36.22, U13.41
RB67: J36.23, U13.42
RB68: J36.24, U13.43
RB69: J36.25, U13.44
RB70: J45.8, U16.25
RB71: J45.7, U16.24
RB72: J44.10, U16.20
RB73: J44.11, U16.21
RB74: J44.12, U16.22
RB75: J45.6, U16.23
RB76: J44.15, U16.32
RB77: J44.16, U16.33
RB78: J44.17, U16.34
RB79: J44.18, U16.35
RB80: J44.22, U16.41
RB81: J44.23, U16.42
RB82: J44.24, U16.43
RB83: J44.25, U16.44
RC1: J3.38, U1.6
RC2: J3.39, U1.7
RC3: J3.40, U1.8
RC4: J4.1, U1.9
RC5: J11.38, U4.6
RC6: J11.39, U4.7
RC7: J11.40, U4.8
RC8: J12.1, U4.9
RC9: C34.1, J11.9, Q4.X1, U4.73
RC10: C33.1, J11.10, Q4.X2, U4.74
RC11: J19.38, U7.6
RC12: J19.39, U7.7
RC13: C17.1, J3.9, Q2.X1, U1.73
RC14: C16.1, J3.10, Q2.X2, U1.74
RC15: J19.40, U7.8
RC16: J20.1, U7.9
RC17: C51.1, J19.9, Q6.X1, U7.73
RC18: C50.1, J19.10, Q6.X2, U7.74
RC19: J27.38, U10.6
RC20: J27.39, U10.7
RC21: J27.40, U10.8
RC22: J28.1, U10.9
RC23: C68.1, J27.9, Q8.X1, U10.73
RC24: C67.1, J27.10, Q8.X2, U10.74
RC25: J35.38, U13.6
RC26: J35.39, U13.7
RC27: J35.40, U13.8
RC28: J36.1, U13.9
RC29: C85.1, J35.9, Q10.X1, U13.73
RC30: C84.1, J35.10, Q10.X2, U13.74
RC31: J43.38, U16.6
RC32: J43.39, U16.7
RC33: J43.40, U16.8
RC34: J44.1, U16.9
RC35: C102.1, J43.9, Q12.X1, U16.73
RC36: C101.1, J43.10, Q12.X2, U16.74
RD0: J3.8, U1.72
RD1: J3.11, U1.76
RD2: J3.12, U1.77
RD3: J3.13, U1.78
RD4: J3.16, U1.81
RD5: J3.17, U1.82
RD6: J3.18, U1.83
RD7: J3.19, U1.84
RD8: J3.4, U1.68
RD9: J3.5, U1.69
RD10: J3.6, U1.70
RD11: J3.7, U1.71
RD12: J3.14, U1.79
RD13: J3.15, U1.80
RD14: J4.26, U1.47
RD15: J4.27, U1.48
RD16: J12.26, U4.47
RD17: J12.27, U4.48
RD18: J11.4, U4.68
RD19: J11.5, U4.69
RD20: J11.6, U4.70
RD21: J11.7, U4.71
RD22: J11.8, U4.72
RD23: J11.11, U4.76
RD24: J11.12, U4.77
RD25: J11.13, U4.78
RD26: J11.14, U4.79
RD27: J11.15, U4.80
RD28: J11.16, U4.81
RD29: J11.17, U4.82
RD30: J11.18, U4.83
RD31: J11.19, U4.84
RD32: J20.26, U7.47
RD33: J20.27, U7.48
RD34: J19.4, U7.68
RD35: J19.5, U7.69
RD36: J19.6, U7.70
RD37: J19.7, U7.71
RD38: J19.8, U7.72
RD39: J19.11, U7.76
RD40: J19.12, U7.77
RD41: J19.13, U7.78
RD42: J19.14, U7.79
RD43: J19.15, U7.80
RD44: J19.16, U7.81
RD45: J19.17, U7.82
RD46: J19.18, U7.83
RD47: J19.19, U7.84
RD48: J28.26, U10.47
RD49: J28.27, U10.48
RD50: J27.4, U10.68
RD51: J27.5, U10.69
RD52: J27.6, U10.70
RD53: J27.7, U10.71
RD54: J27.8, U10.72
RD55: J27.11, U10.76
RD56: J27.12, U10.77
RD57: J27.13, U10.78
RD58: J27.14, U10.79
RD59: J27.15, U10.80
RD60: J27.16, U10.81
RD61: J27.17, U10.82
RD62: J27.18, U10.83
RD63: J27.19, U10.84
RD64: J36.26, U13.47
RD65: J36.27, U13.48
RD66: J35.4, U13.68
RD67: J35.5, U13.69
RD68: J35.6, U13.70
RD69: J35.7, U13.71
RD70: J35.8, U13.72
RD71: J35.11, U13.76
RD72: J35.12, U13.77
RD73: J35.13, U13.78
RD74: J35.14, U13.79
RD75: J35.15, U13.80
RD76: J35.16, U13.81
RD77: J35.17, U13.82
RD78: J35.18, U13.83
RD79: J35.19, U13.84
RD80: J44.26, U16.47
RD81: J44.27, U16.48
RD82: J43.4, U16.68
RD83: J43.5, U16.69
RD84: J43.6, U16.70
RD85: J43.7, U16.71
RD86: J43.8, U16.72
RD87: J43.11, U16.76
RD88: J43.12, U16.77
RD89: J43.13, U16.78
RD90: J43.14, U16.79
RD91: J43.15, U16.80
RD92: J43.16, U16.81
RD93: J43.17, U16.82
RD94: J43.18, U16.83
RD95: J43.19, U16.84
RE0: J3.26, LED3.C, U1.93
RE1: J3.27, LED2.C, U1.94
RE2: J3.31, LED1.C, U1.98
RE3: J3.32, U1.99, USB.C
RE4: J3.33, U1.100
RE5: J3.35, U1.3
RE6: J3.36, R5.2, U1.4, USER.3, USER.4
RE7: J3.37, PROGRAM.3, PROGRAM.4, R3.2, U1.5
RE8: J4.8, U1.18
RE9: J4.9, U1.19
RE10: J12.9, U4.19
RE11: J12.8, U4.18
RE12: J11.35, U4.3
RE13: J11.36, R20.2, U4.4, USER1.3, USER1.4
RE14: J11.37, PROGRAM1.3, PROGRAM1.4, R19.2, U4.5
RE15: J11.26, LED4.C, U4.93
RE16: J11.27, LED5.C, U4.94
RE17: J11.31, LED6.C, U4.98
RE18: J11.32, U4.99, USB1.C
RE19: J11.33, U4.100
RE20: J20.9, U7.19
RE21: J20.8, U7.18
RE22: J19.35, U7.3
RE23: J19.36, R33.2, U7.4, USER2.3, USER2.4
RE24: J19.37, PROGRAM2.3, PROGRAM2.4, R32.2, U7.5
RE25: J19.26, LED7.C, U7.93
RE26: J19.27, LED8.C, U7.94
RE27: J19.31, LED9.C, U7.98
RE28: J19.32, U7.99, USB2.C
RE29: J19.33, U7.100
RE30: J28.9, U10.19
RE31: J28.8, U10.18
RE32: J27.35, U10.3
RE33: J27.36, R46.2, U10.4, USER3.3, USER3.4
RE34: J27.37, PROGRAM3.3, PROGRAM3.4, R45.2, U10.5
RE35: J27.26, LED10.C, U10.93
RE36: J27.27, LED11.C, U10.94
RE37: J27.31, LED12.C, U10.98
RE38: J27.32, U10.99, USB3.C
RE39: J27.33, U10.100
RE40: J36.9, U13.19
RE41: J36.8, U13.18
RE42: J35.35, U13.3
RE43: J35.36, R59.2, U13.4, USER4.3, USER4.4
RE44: J35.37, PROGRAM4.3, PROGRAM4.4, R58.2, U13.5
RE45: J35.26, LED13.C, U13.93
RE46: J35.27, LED14.C, U13.94
RE47: J35.31, LED15.C, U13.98
RE48: J35.32, U13.99, USB4.C
RE49: J35.33, U13.100
RE50: J44.9, U16.19
RE51: J44.8, U16.18
RE52: J43.35, U16.3
RE53: J43.36, R72.2, U16.4, USER5.3, USER5.4
RE54: J43.37, PROGRAM5.3, PROGRAM5.4, R71.2, U16.5
RE55: J43.26, LED16.C, U16.93
RE56: J43.27, LED17.C, U16.94
RE57: J43.31, LED18.C, U16.98
RE58: J43.32, U16.99, USB5.C
RE59: J43.33, U16.100
RF0: J3.20, U1.87
RF1: J3.21, U1.88
RF2: J4.30, U1.52
RF3: J12.20, U4.39
RF4: J4.28, U1.49
RF5: J4.29, U1.50
RF6: J12.21, U4.40
RF7: J12.28, U4.49
RF8: J4.31, U1.53
RF9: J12.29, U4.50
RF10: J12.30, U4.52
RF11: J12.31, U4.53
RF12: J4.21, U1.40
RF13: J4.20, U1.39
RF14: J11.20, U4.87
RF15: J11.21, U4.88
RF16: J20.20, U7.39
RF17: J20.21, U7.40
RF18: J20.28, U7.49
RF19: J20.29, U7.50
RF20: J20.30, U7.52
RF21: J20.31, U7.53
RF22: J19.20, U7.87
RF23: J19.21, U7.88
RF24: J28.20, U10.39
RF25: J28.21, U10.40
RF26: J28.28, U10.49
RF27: J28.29, U10.50
RF28: J28.30, U10.52
RF29: J28.31, U10.53
RF30: J27.20, U10.87
RF31: J27.21, U10.88
RF32: J36.20, U13.39
RF33: J36.21, U13.40
RF34: J36.28, U13.49
RF35: J36.29, U13.50
RF36: J36.30, U13.52
RF37: J36.31, U13.53
RF38: J35.20, U13.87
RF39: J35.21, U13.88
RF40: J44.20, U16.39
RF41: J44.21, U16.40
RF42: J44.28, U16.49
RF43: J44.29, U16.50
RF44: J44.30, U16.52
RF45: J44.31, U16.53
RF46: J43.20, U16.87
RF47: J43.21, U16.88
RG0: J3.23, U1.90
RG1: J3.22, U1.89
RG2: J11.34, U4.1
RG3: J12.3, U4.11
RG4: J12.2, U4.10
RG5: J12.4, U4.12
RG6: J4.2, U1.10
RG7: J4.3, U1.11
RG8: J4.4, U1.12
RG9: J4.6, U1.14
RG10: J12.6, U4.14
RG11: J11.22, U4.89
RG12: J3.29, U1.96
RG13: J3.30, U1.97
RG14: J3.28, U1.95
RG15: J3.34, U1.1
RG16: J11.23, U4.90
RG17: J11.28, U4.95
RG18: J11.29, U4.96
RG19: J11.30, U4.97
RG20: J19.34, U7.1
RG21: J20.3, U7.11
RG22: J20.2, U7.10
RG23: J20.4, U7.12
RG24: J20.6, U7.14
RG25: J19.22, U7.89
RG26: J19.23, U7.90
RG27: J19.28, U7.95
RG28: J19.29, U7.96
RG29: J19.30, U7.97
RG30: J27.34, U10.1
RG31: J28.3, U10.11
RG32: J28.2, U10.10
RG33: J28.4, U10.12
RG34: J28.6, U10.14
RG35: J27.22, U10.89
RG36: J27.23, U10.90
RG37: J27.28, U10.95
RG38: J27.29, U10.96
RG39: J27.30, U10.97
RG40: J35.34, U13.1
RG41: J36.3, U13.11
RG42: J36.2, U13.10
RG43: J36.4, U13.12
RG44: J36.6, U13.14
RG45: J35.22, U13.89
RG46: J35.23, U13.90
RG47: J35.28, U13.95
RG48: J35.29, U13.96
RG49: J35.30, U13.97
RG50: J43.34, U16.1
RG51: J44.3, U16.11
RG52: J44.2, U16.10
RG53: J44.4, U16.12
RG54: J44.6, U16.14
RG55: J43.22, U16.89
RG56: J43.23, U16.90
RG57: J43.28, U16.95
RG58: J43.29, U16.96
RG59: J43.30, U16.97
USBID: J6.4, J8.ID, R9.1, U1.51
USBID1: J9.ID, J14.4, R18.1, U4.51
USBID2: J17.ID, J22.4, R31.1, U7.51
USBID3: J25.ID, J30.4, R44.1, U10.51
USBID4: J33.ID, J38.4, R57.1, U13.51
USBID5: J41.ID, J46.4, R70.1, U16.51
VBUS: C3.1, J6.1, J7.VBUS, J8.VBUS, JP1.2, PWR_SEL.3, PWR_SEL.6, U1.54
VBUS1: C30.1, J9.VBUS, J14.1, J15.VBUS, JP2.2, PWR_SEL1.3, PWR_SEL1.6, U4.54
VBUS2: C47.1, J17.VBUS, J22.1, J23.VBUS, JP3.2, PWR_SEL2.3, PWR_SEL2.6, U7.54
VBUS3: C64.1, J25.VBUS, J30.1, J31.VBUS, JP4.2, PWR_SEL3.3, PWR_SEL3.6, U10.54
VBUS4: C81.1, J33.VBUS, J38.1, J39.VBUS, JP5.2, PWR_SEL4.3, PWR_SEL4.6, U13.54
VBUS5: C98.1, J41.VBUS, J46.1, J47.VBUS, JP6.2, PWR_SEL5.3, PWR_SEL5.6, U16.54
VIN_RAW: C1.A, D1.C, U3.3
VIN_RAW1: C26.A, D2.C, U6.3
VIN_RAW2: C43.A, D3.C, U9.3
VIN_RAW3: C60.A, D4.C, U12.3
VIN_RAW4: C77.A, D5.C, U15.3
VIN_RAW5: C94.A, D6.C, U18.3
VPP: J4.5, J5.1, R10.2, RESET.3, RESET.4, U1.13
VPP1: J12.5, J13.1, R21.2, RESET1.3, RESET1.4, U4.13
VPP2: J20.5, J21.1, R34.2, RESET2.3, RESET2.4, U7.13
VPP3: J28.5, J29.1, R47.2, RESET3.3, RESET3.4, U10.13
VPP4: J36.5, J37.1, R60.2, RESET4.3, RESET4.4, U13.13
VPP5: J44.5, J45.1, R73.2, RESET5.3, RESET5.4, U16.13

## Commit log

2014-08-19 Adding hardware files and README info
2015-09-29 new larger panel
2017-01-10 .brd file Values Updated
2017-01-11 .brd Values Added

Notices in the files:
Hardware/UBW32_MX460_v262.sch:
licenced under Creative Commons v3.0 Attribution licence
parts and their libraries:
SparkFun-Aesthetics: Licensing: CC v3.0 Share-Alike You are welcome to use this library for commercial purposes.
SparkFun-Retired: Licensing:Creative Commons ShareAlike 4.0 International - https://creativecommons.org/licenses/by-sa/4.0
